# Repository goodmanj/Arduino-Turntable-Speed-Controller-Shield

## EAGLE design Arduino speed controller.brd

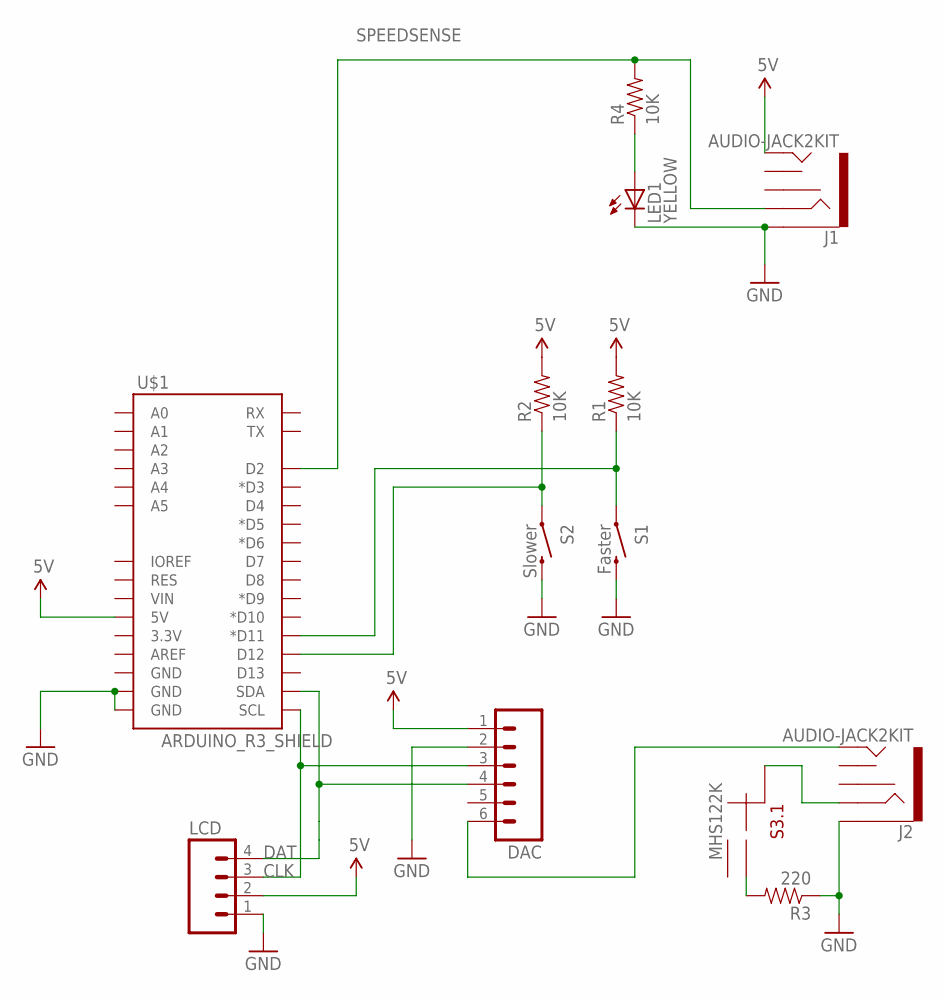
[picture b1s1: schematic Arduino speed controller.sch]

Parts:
DAC: M06SIP; 1X06
J1, J2: AUDIO-JACK2KIT; AUDIO-JACK-KIT
LCD: M04PTH; 1X04
LED1: YELLOW; LED3MM
R1, R2, R4: 10K; AXIAL-0.4
R3: 220; AXIAL-0.4
S1: Faster; TACTILE-PTH
S2: Slower; TACTILE-PTH
S3: MHS122K; APEM-MHS122K
U$1: ARDUINO_R3_SHIELD; UNO_R3_SHIELD

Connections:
5V: DAC.1, J1.TIP, LCD.2, R1.P$2 (2), R2.P$2 (2), U$1.5V
CLK: DAC.3, LCD.3, U$1.SCL
DAT: DAC.4, LCD.4, U$1.SDA
FASTER: R1.P$1 (1), S1.1, U$1.D11 (*D11)
GND: DAC.2, J1.SLEEVE, J2.SLEEVE, LCD.1, LED1.K (C), R3.P$1 (1), S1.3 (2), S2.3 (2), U$1.GND@0 (GND), U$1.GND@1 (GND)
unnamed: J2.RING, S3.CMN (CM)
unnamed: R3.P$2 (2), S3.1
unnamed: DAC.6, J2.TIP
unnamed: LED1.A, R4.P$1 (1)
SLOWER: R2.P$1 (1), S2.1, U$1.D12
SPEEDSENSE: J1.RING, R4.P$2 (2), U$1.D2

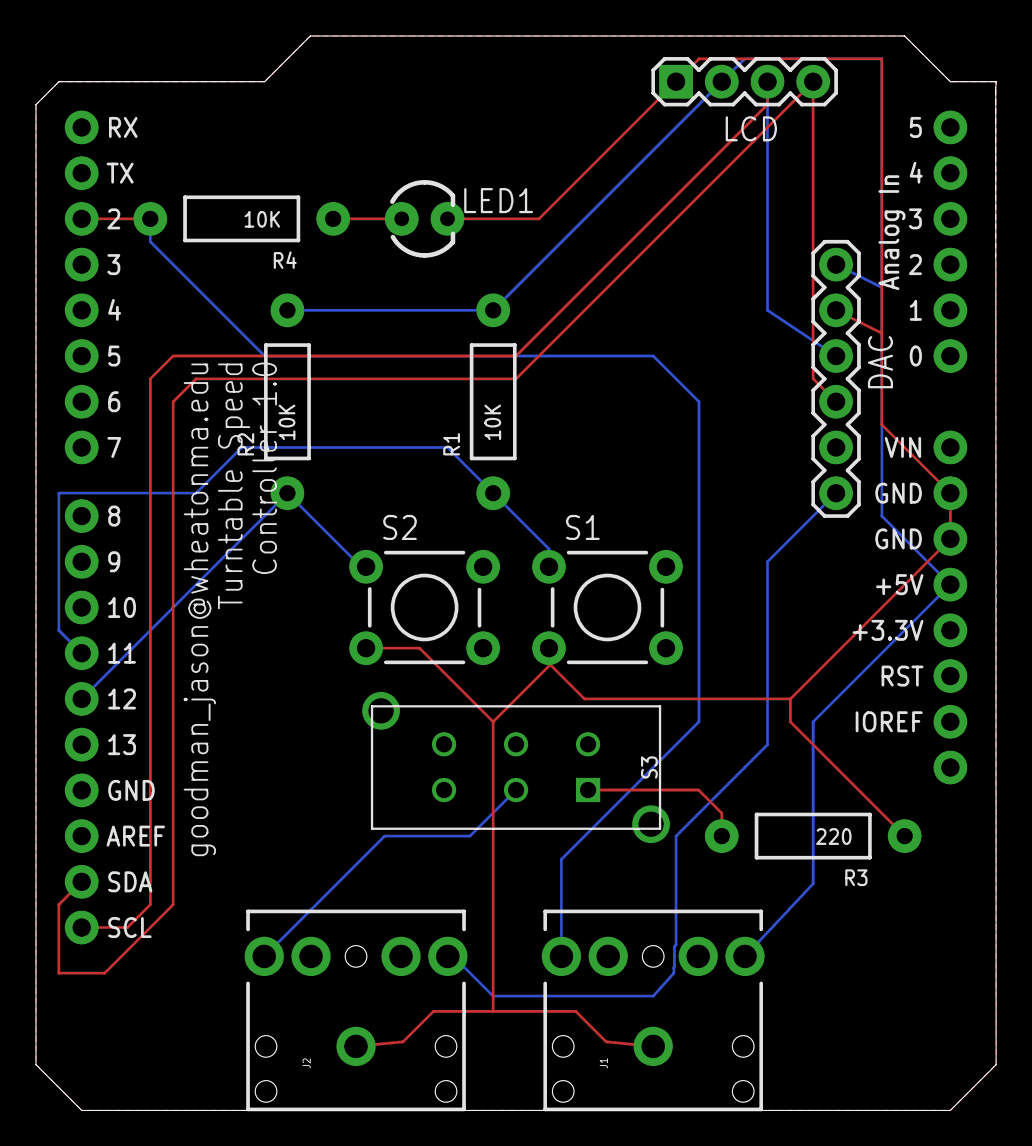
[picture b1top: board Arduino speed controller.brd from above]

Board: 2 copper layers, 53.3 x 59.7 mm, 13 parts (0 on the bottom side), 11 nets.

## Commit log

2018-06-14 Initial commit
    Arduino-based speed controller for geophysical fluid dynamics
    turntables designed and built by Dana Sigall.
2018-06-14 Ignore .pro files.
2018-06-14 Copper fills (disabled), moved jacks
2018-07-14 Added DAC
    Added DAC

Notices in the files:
parts and their libraries:
SparkFun-Connectors: Licensing: CC v3.0 Share-Alike You are welcome to use this library for commercial purposes.
